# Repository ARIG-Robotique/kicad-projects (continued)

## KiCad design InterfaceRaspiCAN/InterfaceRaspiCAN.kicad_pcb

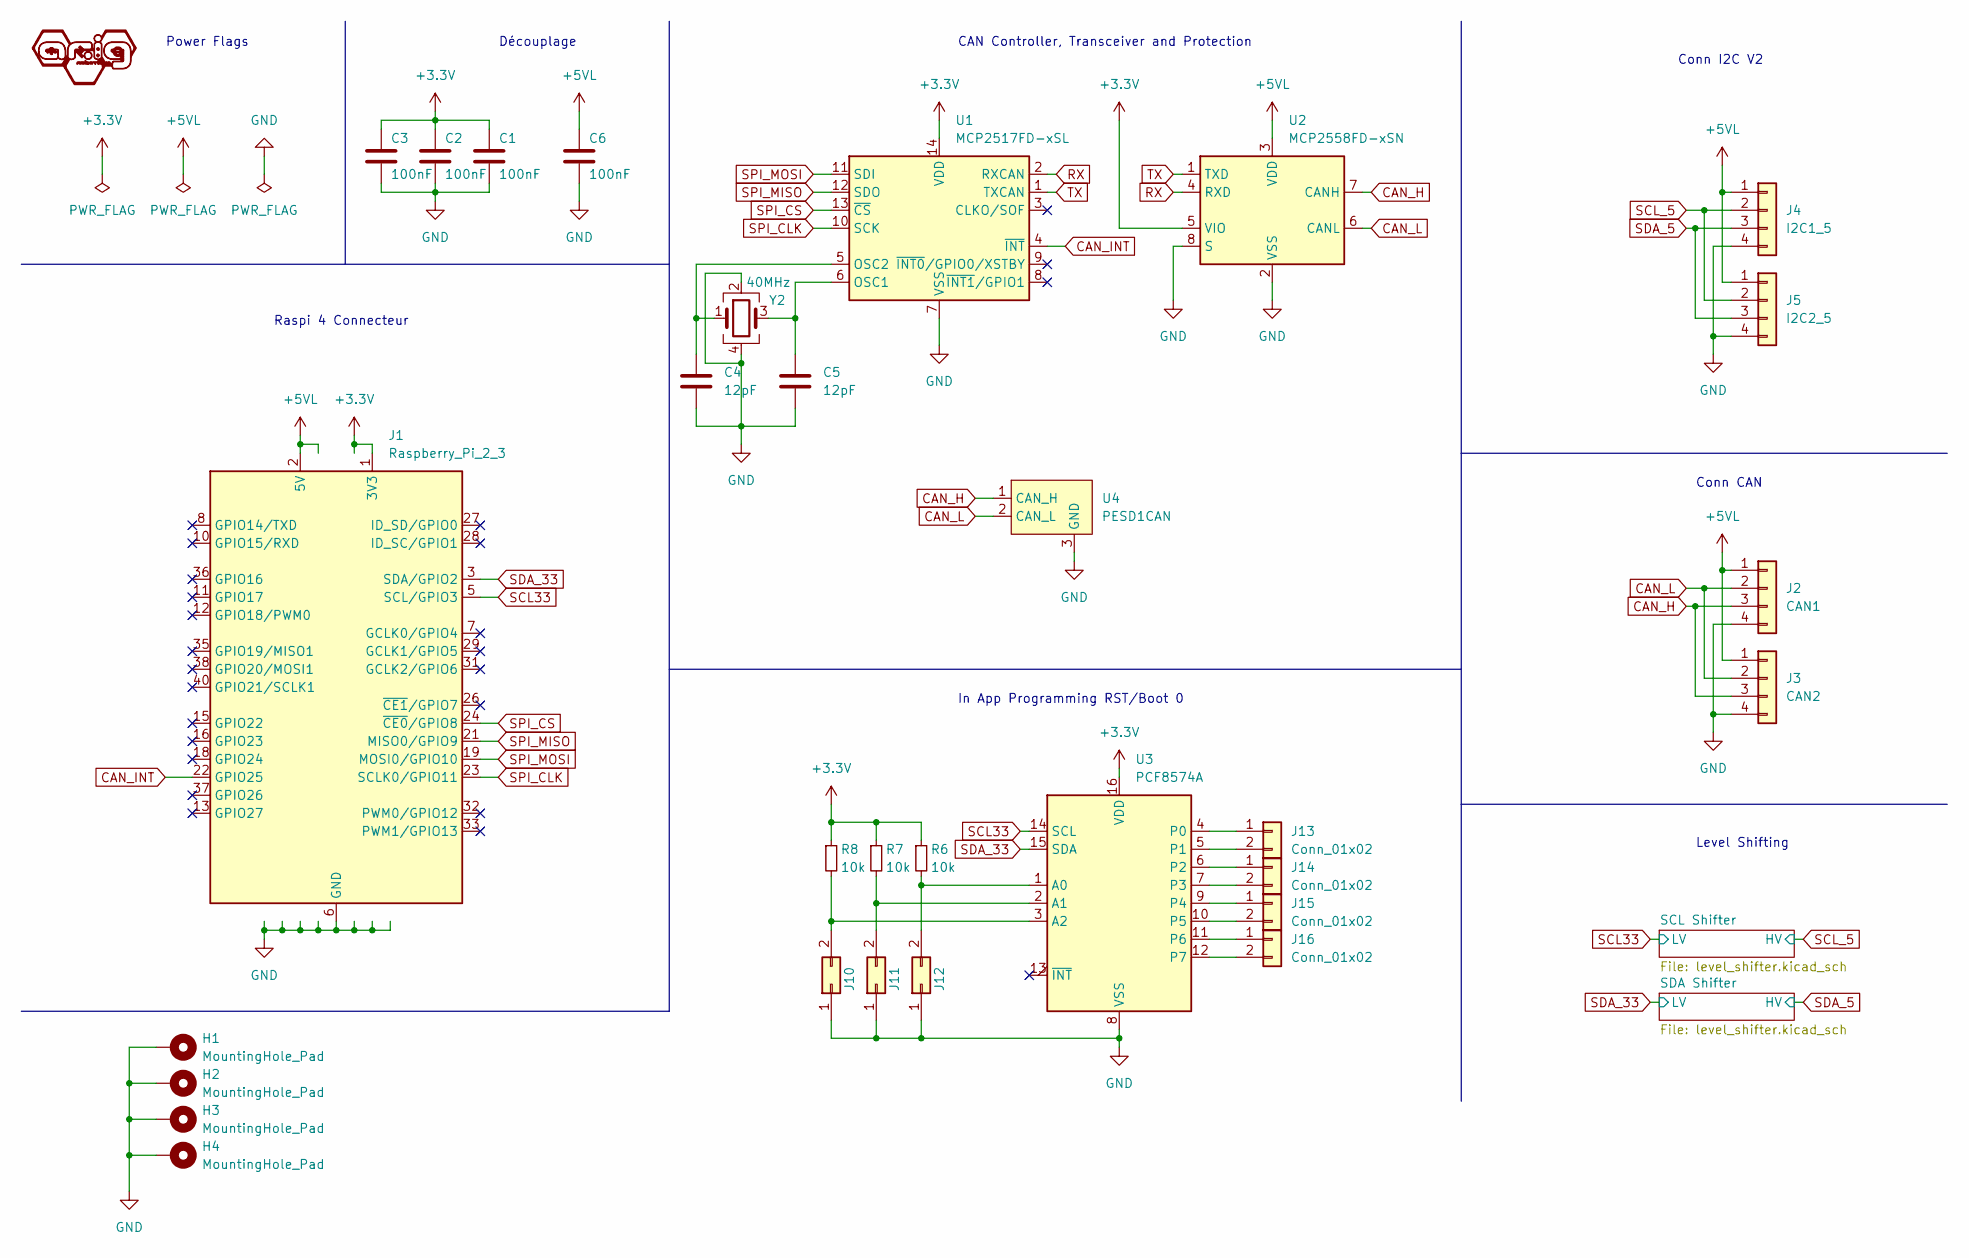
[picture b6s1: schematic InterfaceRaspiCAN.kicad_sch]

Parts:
C1, C2, C3, C6: 100nF; C_0402_1005Metric_Pad0.74x0.62mm_HandSolder; LCSC Part C1525
C4, C5: 12pF; C_0402_1005Metric_Pad0.74x0.62mm_HandSolder; LCSC Part C1547
H1, H2, H3, H4: MountingHole_Pad; MountingHole_2.7mm_M2.5_Pad_Via
J1: Raspberry_Pi_2_3; PinSocket_2x20_P2.54mm_Vertical
J2: CAN1; JST_PH_S4B-PH-K_1x04_P2.00mm_Horizontal
J3: CAN2; JST_PH_S4B-PH-K_1x04_P2.00mm_Horizontal
J4: I2C1_5; JST_PH_S4B-PH-K_1x04_P2.00mm_Horizontal
J5: I2C2_5; JST_PH_S4B-PH-K_1x04_P2.00mm_Horizontal
J10, J11, J12: Conn_02x01; SolderJumper-2_P1.3mm_Open_RoundedPad1.0x1.5mm
J13, J14, J15, J16: Conn_01x02; JST_PH_S2B-PH-K_1x02_P2.00mm_Horizontal
R6, R7, R8: 10k; R_0805_2012Metric_Pad1.20x1.40mm_HandSolder; LCSC Part C17414
U1: MCP2517FD-xSL; SOIC-14_3.9x8.7mm_P1.27mm; LCSC Part C133861
U2: MCP2558FD-xSN; SOIC-8_3.9x4.9mm_P1.27mm; LCSC Part C124015
U3: PCF8574A; SOIC-16W_7.5x10.3mm_P1.27mm; LCSC Part C7605
U4: PESD1CAN; SOT-23; LCSC Part C907838
Y2: 40MHz; Crystal_SMD_3225-4Pin_3.2x2.5mm_HandSoldering; LCSC Part C252255

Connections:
+3.3V: C1.1, C2.1, C3.1, J1.1 (3V3), J1.17 (3V3), R6.1, R7.1, R8.1, U1.14 (VDD), U2.5 (VIO), U3.16 (VDD); also elsewhere on the board
+5VL: C6.1, J1.2 (5V), J1.4 (5V), J2.1, J3.1, J4.1, J5.1, U2.3 (VDD); also elsewhere on the board
CAN_H: J2.3, J3.3, U2.7 (CANH), U4.1 (CAN_H)
CAN_INT: J1.22 (GPIO25), U1.4 (~INT)
CAN_L: J2.2, J3.2, U2.6 (CANL), U4.2 (CAN_L)
GND: C1.2, C2.2, C3.2, C4.2, C5.2, C6.2, H1.1, H2.1, H3.1, H4.1, J1.6 (GND), J1.9 (GND), J1.14 (GND), J1.20 (GND), J1.25 (GND), J1.30 (GND), J1.34 (GND), J1.39 (GND), J2.4, J3.4, J4.4, J5.4, J10.1, J11.1, J12.1, U1.7 (VSS), U2.2 (VSS), U2.8 (S), U3.8 (VSS), U4.3 (GND), Y2.2, Y2.4
unnamed: J10.2, R8.2, U3.3 (A2)
unnamed: J11.2, R7.2, U3.2 (A1)
unnamed: J12.2, R6.2, U3.1 (A0)
unnamed: J13.1, U3.4 (P0)
unnamed: J13.2, U3.5 (P1)
unnamed: J14.1, U3.6 (P2)
unnamed: J14.2, U3.7 (P3)
unnamed: J15.1, U3.9 (P4)
unnamed: J15.2, U3.10 (P5)
unnamed: J16.1, U3.11 (P6)
unnamed: J16.2, U3.12 (P7)
unnamed: C5.1, U1.6 (OSC1), Y2.3
unnamed: C4.1, U1.5 (OSC2), Y2.1
RX: U1.2 (RXCAN), U2.4 (RXD)
SCL33: J1.5 (SCL/GPIO3), U3.14 (SCL); also elsewhere on the board
SCL_5: J4.2, J5.2; also elsewhere on the board
SDA_5: J4.3, J5.3; also elsewhere on the board
SDA_33: J1.3 (SDA/GPIO2), U3.15 (SDA); also elsewhere on the board
SPI_CLK: J1.23 (SCLK0/GPIO11), U1.10 (SCK)
SPI_CS: J1.24 (~CE0/GPIO8), U1.13 (~CS)
SPI_MISO: J1.21 (MISO0/GPIO9), U1.12 (SDO)
SPI_MOSI: J1.19 (MOSI0/GPIO10), U1.11 (SDI)
TX: U1.1 (TXCAN), U2.1 (TXD)

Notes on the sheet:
In App Programming RST/Boot 0
Power Flags
Conn I2C V2
CAN Controller, Transceiver and Protection
Raspi 4 Connecteur
Level Shifting
Conn CAN
Découplage

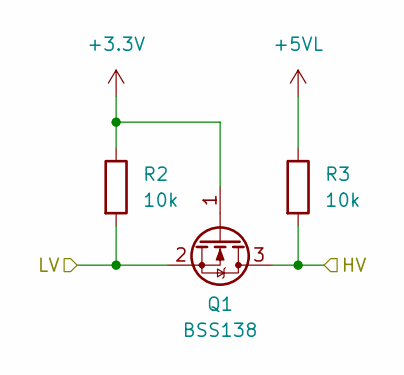
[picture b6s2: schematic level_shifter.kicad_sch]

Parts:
Q1: BSS138; SOT-23; LCSC Part C426569
R2, R3: 10k; R_0805_2012Metric_Pad1.20x1.40mm_HandSolder; LCSC Part C17414

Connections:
+3.3V: Q1.1 (G), R2.1; also elsewhere on the board
+5VL: R3.1; also elsewhere on the board
SCL33: Q1.2 (S), R2.2; also elsewhere on the board
SCL_5: Q1.3 (D), R3.2; also elsewhere on the board

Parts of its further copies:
Q2: BSS138; SOT-23; LCSC Part C426569
R4, R5: 10k; R_0805_2012Metric_Pad1.20x1.40mm_HandSolder; LCSC Part C17414

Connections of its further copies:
+3.3V: Q2.1 (G), R4.1; also elsewhere on the board
+5VL: R5.1; also elsewhere on the board
SDA_5: Q2.3 (D), R5.2; also elsewhere on the board
SDA_33: Q2.2 (S), R4.2; also elsewhere on the board

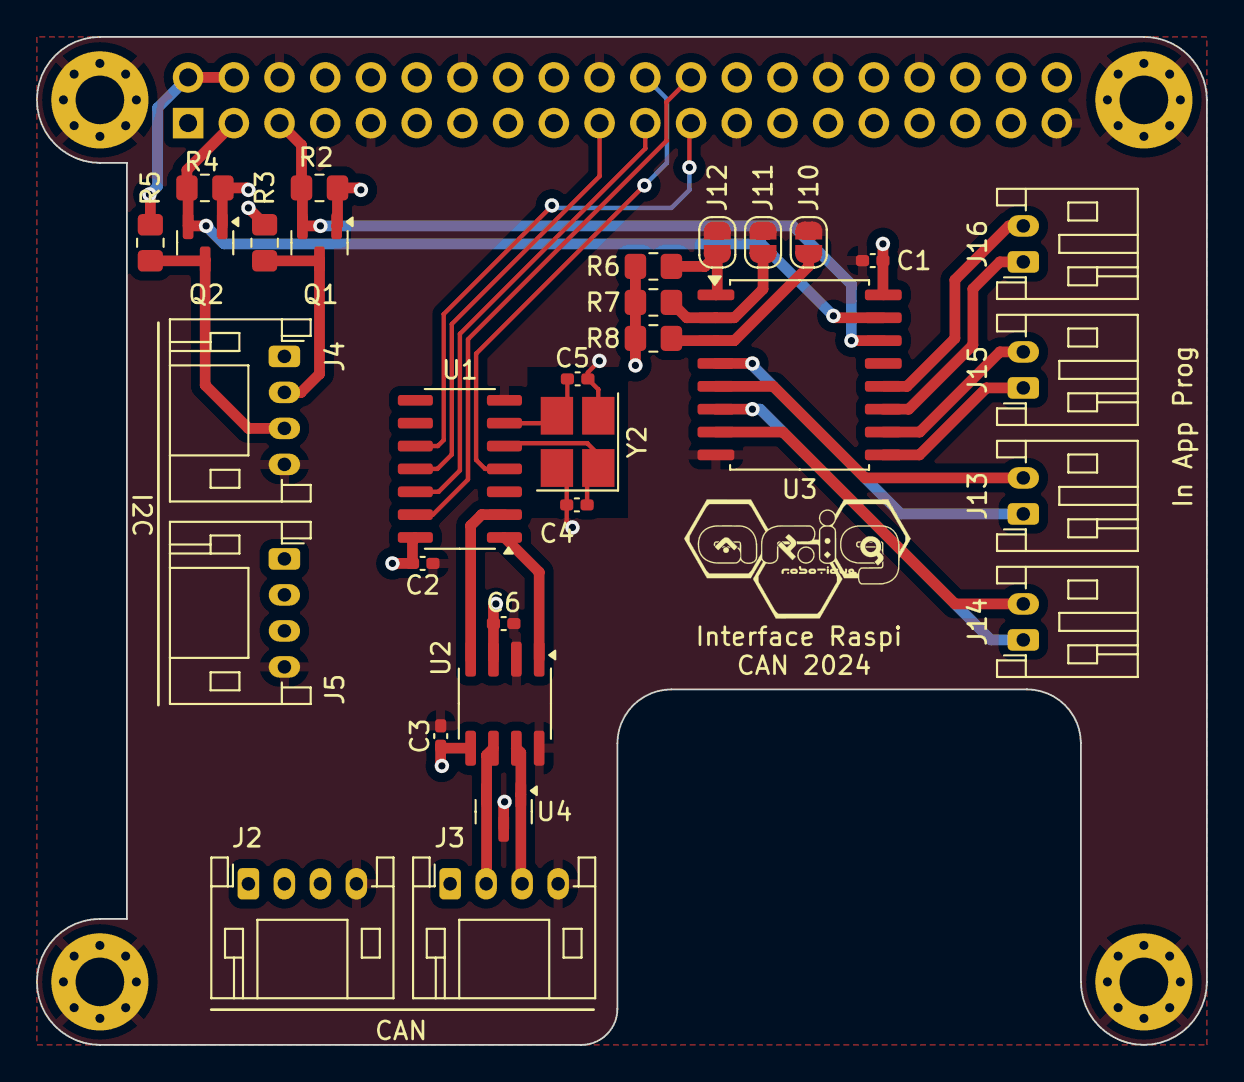
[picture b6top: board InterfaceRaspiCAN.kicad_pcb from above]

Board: 4 copper layers, 65.0 x 56.0 mm, 36 parts (1 on the bottom side), 29 nets.

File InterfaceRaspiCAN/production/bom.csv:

Designator,Footprint,Quantity,Value,LCSC Part #
"C1, C2, C3, C6",0402,4,100nF,C1525
"C4, C5",0402,2,12pF,C1547
"H1, H2, H3, H4",MountingHole_2.7mm_M2.5_Pad_Via,4,MountingHole_Pad,
J1,PinSocket_2x20_P2.54mm_Vertical,1,Raspberry_Pi_2_3,
"J10, J11, J12",SolderJumper-2_P1.3mm_Open_RoundedPad1.0x1.5mm,3,Conn_02x01,
"J13, J14, J15, J16",JST_PH_S2B-PH-K_1x02_P2.00mm_Horizontal,4,Conn_01x02,
J2,JST_PH_S4B-PH-K_1x04_P2.00mm_Horizontal,1,CAN1,
J3,JST_PH_S4B-PH-K_1x04_P2.00mm_Horizontal,1,CAN2,
J4,JST_PH_S4B-PH-K_1x04_P2.00mm_Horizontal,1,I2C1_5,
J5,JST_PH_S4B-PH-K_1x04_P2.00mm_Horizontal,1,I2C2_5,
"Q1, Q2",SOT-23,2,BSS138,C426569
"R2, R3, R4, R5, R6, R7, R8",0805,7,10k,C17414
U1,SOIC-14_3.9x8.7mm_P1.27mm,1,MCP2517FD-xSL,C133861
U2,SOIC-8_3.9x4.9mm_P1.27mm,1,MCP2558FD-xSN,C124015
U3,SOIC-16W_7.5x10.3mm_P1.27mm,1,PCF8574A,C7605
U4,SOT-23,1,PESD1CAN,C907838
Y2,Crystal_SMD_3225-4Pin_3.2x2.5mm_HandSoldering,1,40MHz, C252255

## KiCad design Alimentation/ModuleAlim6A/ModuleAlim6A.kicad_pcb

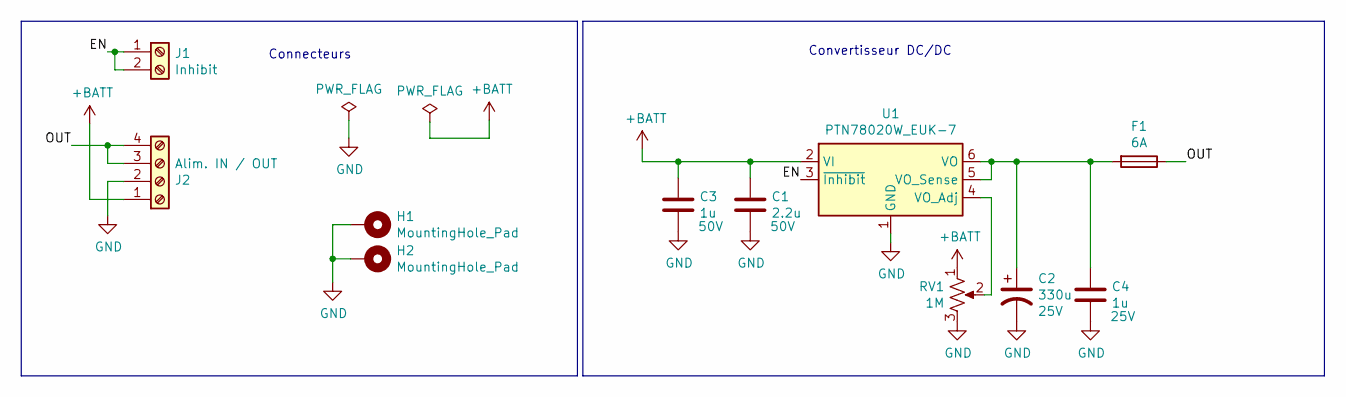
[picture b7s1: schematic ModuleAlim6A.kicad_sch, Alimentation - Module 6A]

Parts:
C1: 2.2u; C_1206_3216Metric_Pad1.33x1.80mm_HandSolder; LCSC Part C50254
C2: 330u; CP_Elec_8x10; LCSC Part C134842
C3: 1u; C_0805_2012Metric_Pad1.18x1.45mm_HandSolder; LCSC Part C28323
C4: 1u; C_0402_1005Metric_Pad0.74x0.62mm_HandSolder; LCSC Part C52923
F1: 6A; Fuseholder_Cylinder-5x20mm_Schurter_0031_8201_Horizontal_Op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; JLCPCB BOM 0
H1, H2: MountingHole_Pad; MountingHole_3.2mm_M3_Pad_Via; JLCPCB BOM 0
J1: Inhibit; TerminalBlock_Phoenix_MPT-0,5-2-2.54_1x02_P2.54mm_Horizontal; JLCPCB BOM 0
J2: Alim. IN / OUT; TerminalBlock_Phoenix_MKDS-1,5-4-5.08_1x04_P5.08mm_Horizont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; JLCPCB BOM 0
RV1: 1M; Potentiometer_Bourns_3266Y_Vertical; JLCPCB BOM 0
U1: PTN78020W_EUK-7; Texas_EUK_R-PDSS-T7_THT; JLCPCB BOM 0

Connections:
+BATT: C1.1, C3.1, J2.1, RV1.1, U1.2 (VI)
/EN: J1.1, J1.2, U1.3 (~Inhibit)
/OUT: F1.1, J2.3, J2.4
GND: C1.2, C2.2, C3.2, C4.2, H1.1, H2.1, J2.2, RV1.3, U1.1 (GND), U1.7 (GND)
unnamed: C2.1, C4.1, F1.2, U1.5 (VO_Sense), U1.6 (VO)
unnamed: RV1.2, U1.4 (VO_Adj)

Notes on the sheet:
Connecteurs
Convertisseur DC/DC

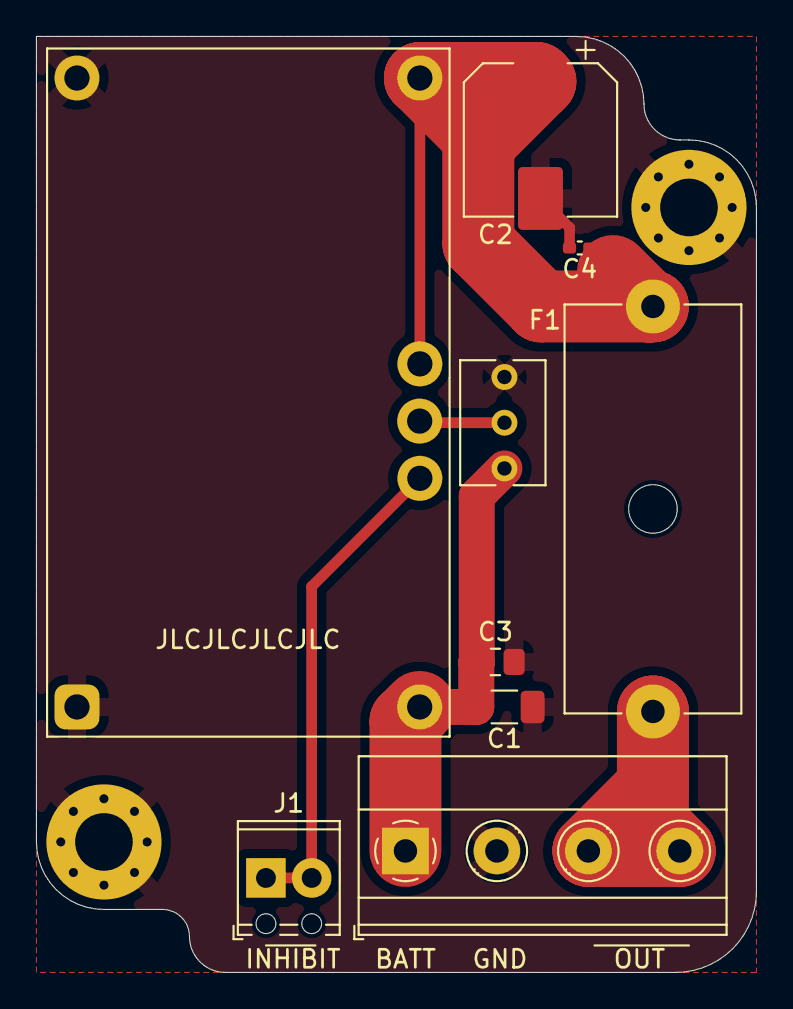
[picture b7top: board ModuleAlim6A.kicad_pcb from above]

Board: 2 copper layers, 40.0 x 52.0 mm, 11 parts (0 on the bottom side), 6 nets.

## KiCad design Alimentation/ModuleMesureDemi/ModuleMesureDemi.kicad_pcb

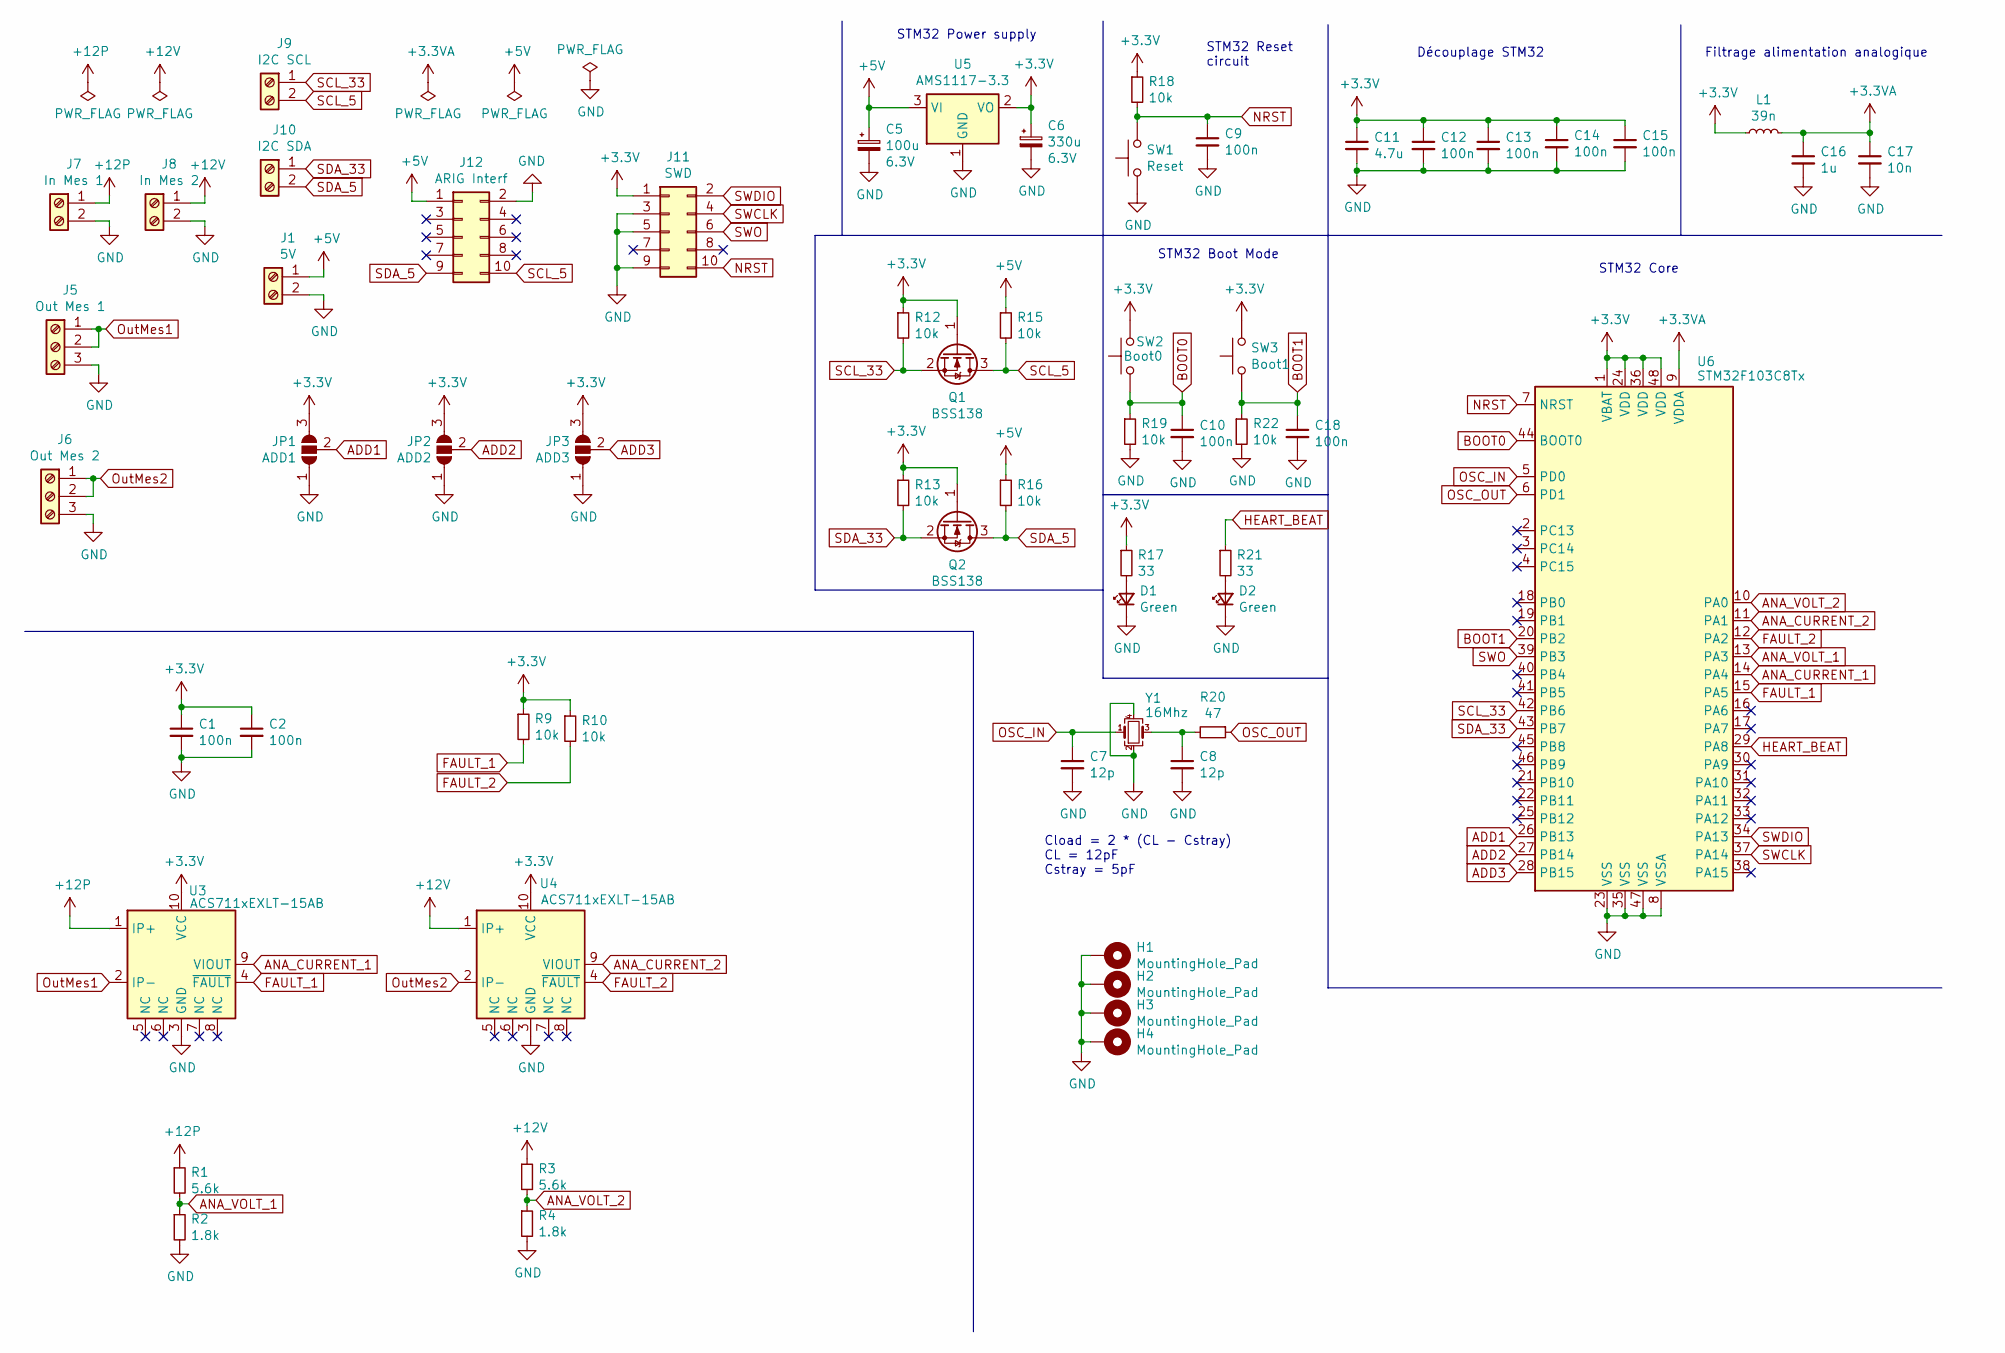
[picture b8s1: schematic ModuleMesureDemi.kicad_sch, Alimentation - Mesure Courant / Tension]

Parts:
C1, C2, C9, C10, C12, C13, C14, C15, C18: 100n; C_0402_1005Metric_Pad0.74x0.62mm_HandSolder; LCSC Part C1525
C5: 100u; CP_Elec_5x5.3; LCSC Part C249463
C6: 330u; CP_Elec_6.3x7.7; LCSC Part C249900
C7, C8: 12p; C_0402_1005Metric_Pad0.74x0.62mm_HandSolder; LCSC Part C1547
C11: 4.7u; C_0402_1005Metric_Pad0.74x0.62mm_HandSolder; LCSC Part C23733
C16: 1u; C_0402_1005Metric_Pad0.74x0.62mm_HandSolder; LCSC Part C52923
C17: 10n; C_0402_1005Metric_Pad0.74x0.62mm_HandSolder; LCSC Part C15195
D1, D2: Green; LED_0805_2012Metric_Pad1.15x1.40mm_HandSolder; LCSC Part C63855
H1, H2, H3, H4: MountingHole_Pad; MountingHole_3.2mm_M3_Pad_Via; JLCPCB BOM 0
J1: 5V; TerminalBlock_Phoenix_MPT-0,5-2-2.54_1x02_P2.54mm_Horizontal; JLCPCB BOM 0
J5: Out Mes 1; TerminalBlock_Phoenix_MKDS-1,5-3-5.08_1x03_P5.08mm_Horizont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; JLCPCB BOM 0
J6: Out Mes 2; TerminalBlock_Phoenix_MKDS-1,5-3-5.08_1x03_P5.08mm_Horizont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; JLCPCB BOM 0
J7: In Mes 1; TerminalBlock_Phoenix_MKDS-1,5-2-5.08_1x02_P5.08mm_Horizont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; JLCPCB BOM 0
J8: In Mes 2; TerminalBlock_Phoenix_MKDS-1,5-2-5.08_1x02_P5.08mm_Horizont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; JLCPCB BOM 0
J9: I2C SCL; TerminalBlock_Phoenix_MPT-0,5-2-2.54_1x02_P2.54mm_Horizontal; JLCPCB BOM 0
J10: I2C SDA; TerminalBlock_Phoenix_MPT-0,5-2-2.54_1x02_P2.54mm_Horizontal; JLCPCB BOM 0
J11: SWD; PinHeader_2x05_P1.27mm_Vertical; JLCPCB BOM 0
J12: ARIG Interf; IDC-Header_2x05_P2.54mm_Vertical; JLCPCB BOM 0
JP1: ADD1; SolderJumper-3_P1.3mm_Open_RoundedPad1.0x1.5mm; JLCPCB BOM 0
JP2: ADD2; SolderJumper-3_P1.3mm_Open_RoundedPad1.0x1.5mm; JLCPCB BOM 0
JP3: ADD3; SolderJumper-3_P1.3mm_Open_RoundedPad1.0x1.5mm; JLCPCB BOM 0
L1: 39n; L_0402_1005Metric_Pad0.77x0.64mm_HandSolder; LCSC Part C26443
Q1, Q2: BSS138; SOT-23; LCSC Part C112239
R1, R3: 5.6k; R_0805_2012Metric_Pad1.20x1.40mm_HandSolder; LCSC Part C26024
R2, R4: 1.8k; R_0805_2012Metric_Pad1.20x1.40mm_HandSolder; LCSC Part C17398
R9, R10, R12, R13, R15, R16, R18, R19, R22: 10k; R_0805_2012Metric_Pad1.20x1.40mm_HandSolder; LCSC Part C17414
R17, R21: 33; R_0805_2012Metric_Pad1.20x1.40mm_HandSolder; LCSC Part C17634
R20: 47; R_0402_1005Metric_Pad0.72x0.64mm_HandSolder; LCSC Part C25118
SW1: Reset; SW_SPST_B3U-1000P; LCSC Part C231329
SW2: Boot0; SW_SPST_B3U-1000P; LCSC Part C231329
SW3: Boot1; SW_SPST_B3U-1000P; LCSC Part C231329
U3, U4: ACS711xEXLT-15AB; Allegro_QFN-12-10-1EP_3x3mm_P0.5mm; LCSC Part C150824
U5: AMS1117-3.3; SOT-223-3_TabPin2; LCSC Part C6186
U6: STM32F103C8Tx; LQFP-48_7x7mm_P0.5mm; LCSC Part C8734
Y1: 16Mhz; Crystal_SMD_3225-4Pin_3.2x2.5mm_HandSoldering; LCSC Part C13738

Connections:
+3.3VA: C16.1, C17.1, L1.2, U6.9 (VDDA)
+3V3: C1.1, C2.1, C6.1, C11.1, C12.1, C13.1, C14.1, C15.1, J11.1, JP1.3 (B), JP2.3 (B), JP3.3 (B), L1.1, Q1.1 (G), Q2.1 (G), R9.1, R10.1, R12.1, R13.1, R17.1, R18.1, SW2.2, SW3.2, U3.10 (VCC), U4.10 (VCC), U5.2 (VO), U6.1 (VBAT), U6.24 (VDD), U6.36 (VDD), U6.48 (VDD)
+5V: C5.1, J1.1, J12.1, R15.1, R16.1, U5.3 (VI)
+12P: J7.1, R1.1, U3.1 (IP+)
+12V: J8.1, R3.1, U4.1 (IP+)
ADD1: JP1.2 (C), U6.26 (PB13)
ADD2: JP2.2 (C), U6.27 (PB14)
ADD3: JP3.2 (C), U6.28 (PB15)
ANA_CURRENT_1: U3.9 (VIOUT), U6.14 (PA4)
ANA_CURRENT_2: U4.9 (VIOUT), U6.11 (PA1)
ANA_VOLT_1: R1.2, R2.1, U6.13 (PA3)
ANA_VOLT_2: R3.2, R4.1, U6.10 (PA0)
BOOT0: C10.1, R19.1, SW2.1, U6.44 (BOOT0)
BOOT1: C18.1, R22.1, SW3.1, U6.20 (PB2)
FAULT_1: R9.2, U3.4 (~FAULT), U6.15 (PA5)
FAULT_2: R10.2, U4.4 (~FAULT), U6.12 (PA2)
GND: C1.2, C2.2, C5.2, C6.2, C7.2, C8.2, C9.2, C10.2, C11.2, C12.2, C13.2, C14.2, C15.2, C16.2, C17.2, C18.2, D1.1 (K), D2.1 (K), H1.1, H2.1, H3.1, H4.1, J1.2, J5.3, J6.3, J7.2, J8.2, J11.3, J11.5, J11.9, J12.2, JP1.1 (A), JP2.1 (A), JP3.1 (A), R2.2, R4.2, R19.2, R22.2, SW1.1, U3.3 (GND), U4.3 (GND), U5.1 (GND), U6.8 (VSSA), U6.23 (VSS), U6.35 (VSS), U6.47 (VSS), Y1.2, Y1.4
HEART_BEAT: R21.1, U6.29 (PA8)
NRST: C9.1, J11.10, R18.2, SW1.2, U6.7 (NRST)
unnamed: C8.1, R20.2, Y1.3
unnamed: D1.2 (A), R17.2
unnamed: D2.2 (A), R21.2
OSC_IN: C7.1, U6.5 (PD0), Y1.1
OSC_OUT: R20.1, U6.6 (PD1)
OutMes1: J5.1, J5.2, U3.2 (IP-)
OutMes2: J6.1, J6.2, U4.2 (IP-)
SCL_5: J9.2, J12.10, Q1.3 (D), R15.2
SCL_33: J9.1, Q1.2 (S), R12.2, U6.42 (PB6)
SDA_5: J10.2, J12.9, Q2.3 (D), R16.2
SDA_33: J10.1, Q2.2 (S), R13.2, U6.43 (PB7)
SWCLK: J11.4, U6.37 (PA14)
SWDIO: J11.2, U6.34 (PA13)
SWO: J11.6, U6.39 (PB3)

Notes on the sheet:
Découplage STM32
STM32 Reset circuit
STM32 Boot Mode
STM32 Core
STM32 Power supply
Cload = 2 * (CL - Cstray) CL = 12pF Cstray = 5pF
Filtrage alimentation analogique

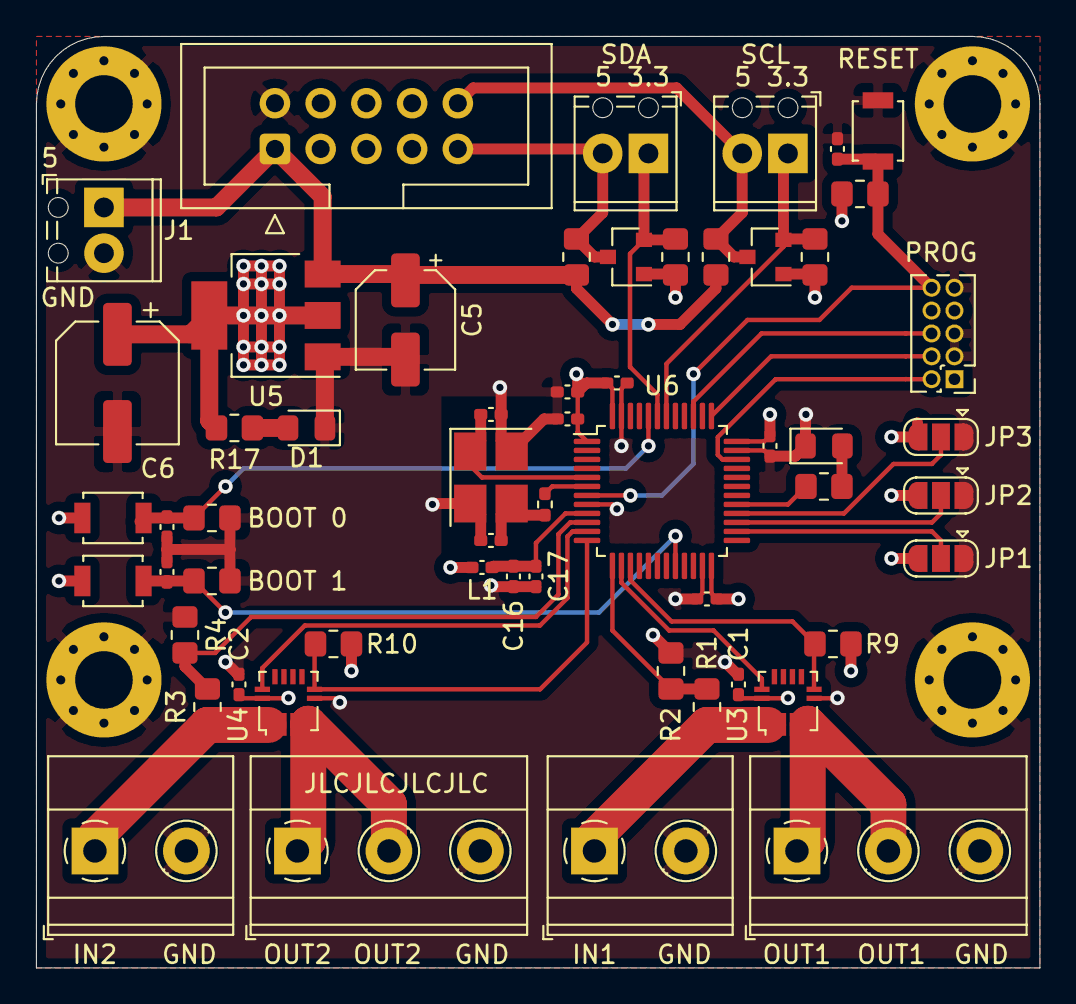
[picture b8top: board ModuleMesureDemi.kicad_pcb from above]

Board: 4 copper layers, 55.8 x 51.8 mm, 61 parts (0 on the bottom side), 33 nets.

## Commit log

2020-11-18 Carte capteur numérique SMD
2020-11-25 Master alimentation SMD
2020-11-25 Capteurs num production
2020-11-25 Library & footprints
2020-11-26 Dimensionnement et récupération des part LCSC
2020-11-30 Finalisation routage carte alim maitre
2020-11-30 Ajout logo ARIG pour la sérigraphie
2020-11-30 Module alimentation 6A
2020-12-01 Alim STm32 + module 3A
2020-12-07 Module alim ISO, clean master alim
2020-12-10 Modules Alim 3A et 6A uniforme sans mesure courant/tension
2020-12-13 Finalisation modules 3A et 6A, routage master alim
2020-12-15 Finalisation routage master alim
2020-12-15 Ignore fichier step
2020-12-17 Rework suite point robot
2020-12-17 Init module alimentation mesure
2021-01-17 Finalisation alimentations
2021-01-17 Carte de mesure de courant et de tension
2021-02-15 Finalisation pour commande pack Alimentation 14/02/2021
2021-02-26 Multiplexeur de capteur couleur (TCS34725)
    # Liste des mots clés de titre de commit (version courte -> résultat long)
    # r <num> -> Récupération du Redmine (Redmine #<num> : <titre_du_redmine>)
    # t <titre> -> Technique : <titre>
    # f <titre> -> Fix : <titre>
    # ty <titre> -> Typo : <titre>
    # d <titre> -> Doc : <titre>
2021-03-11 Potar THT module 3A
    # Liste des mots clés de titre de commit (version courte -> résultat long)
    # r <num> -> Récupération du Redmine (Redmine #<num> : <titre_du_redmine>)
    # t <titre> -> Technique : <titre>
    # f <titre> -> Fix : <titre>
    # ty <titre> -> Typo : <titre>
    # d <titre> -> Doc : <titre>
2021-03-20 Contrôleur de pompes à vide autonome
    # Liste des mots clés de titre de commit (version courte -> résultat long)
    # r <num> -> Récupération du Redmine (Redmine #<num> : <titre_du_redmine>)
    # t <titre> -> Technique : <titre>
    # f <titre> -> Fix : <titre>
    # ty <titre> -> Typo : <titre>
    # d <titre> -> Doc : <titre>
2021-03-22 Interfaces Raspberry PI
    # Liste des mots clés de titre de commit (version courte -> résultat long)
    # r <num> -> Récupération du Redmine (Redmine #<num> : <titre_du_redmine>)
    # t <titre> -> Technique : <titre>
    # f <titre> -> Fix : <titre>
    # ty <titre> -> Typo : <titre>
    # d <titre> -> Doc : <titre>
2021-04-07 Ajout des rendus 3D
2021-04-08 Réduction de taille rail alimentation (fusion borniers)
2021-04-08 Ajout bornier alim 5V sur controleur pompes
2021-04-08 Finalisation interf Raspi
2021-04-08 Ajout bornier alim 5V sur multiplexeur couleur
2021-04-18 Finalisation multiplexeur couleur
2021-04-18 Finalisation interface Raspi
2021-04-18 Re génération des modules alim pour le README
2021-04-18 Ajout empreinte pour switch tactile SMD TS 1088
2021-04-18 Ajout 4 inputs TOR sur le contrôleur pompes
2021-04-18 Finalisation rail alimentation
2021-04-22 Fix Master Alim : affichage statut AU
2021-04-22 Fix module alim 3A : sérigraphie
2021-04-22 Fix images rikiki
2021-05-02 Erreur entre la sérigraphie et l'assignation des PIN
2021-12-12 Ajout Seeeduino XIAO
2021-12-12 Init projet pour la détection des carrés de fouilles
2021-12-12 Cache controlleurs pompes
2022-03-08 Ajout du PCB de detection des carrés de fouilles
2022-03-13 Kicad 6 symbol library
2022-03-13 Arduino Nano 3D model
2022-03-13 Detecteur Carre fouille (pour 2022 en tous cas)
2022-03-24 Répertoire de sortie des fichiers de production
2023-12-11 Add HAT Raspi with CAN, In App Prog and I2C
2023-12-11 Upgrade symbol library to Kicad 7
2023-12-11 Add symbol PESD1CAN (can bus electrostatic protection)
2023-12-12 Fix footprint for PCF8575
2023-12-12 Add PCB for RaspiCAN
2023-12-14 Add ignore for KiCad 7 format
2023-12-14 Upgrade to KiCad 7 some PCB
    - MasterAlimSTM32
    - Capteurs numerique
    - Controleurs pompes
    - Detecteur carre fouille
    - Interface Raspi (without CAN)
2023-12-14 Changes from discussion on meetings
    - Remove 2x I2C connectors
    - Remove 4x InApp programming connectors
    - Change PCF8575 to PCF8574
    - Change a half connectors to horizontal version
2023-12-20 Init project for Asserv Controller
2023-12-21 Upgrade vacuum controller
2023-12-21 Modification for InterfaceRaspiCAN
2023-12-21 Move asserv controller to the right place
2024-01-01 Upgrade base schematics
2024-01-01 Add template for STM32 with CAN
2024-01-03 Add coders & motors interface
2024-01-03 Finalize placement for AsservController
2024-01-03 Change inApp prog, CAN & I2C connectors
2024-01-08 Init routing
2024-01-16 Upgrade alim to Kicad 7
2024-01-16 Add routing on controller asserv
2024-01-16 Add master alim CAN
2024-01-16 Update MasterAlim to Kicad 7
2024-01-16 Update ModuleMesure to Kicad 7
2024-01-18 Add some routes to ControlleursAsserv
2024-02-06 Upgrade AlimMesureDemi to Kicad 7
2024-02-06 Upgrade module Alim6A to Kicad7
2024-02-06 Restructure schematics of AlimCAN
2024-02-07 Add size value in layer comments
2024-02-07 Init placement for MasterAlimCAN
2024-02-07 Last save for today
2024-02-07 Fix 3D model for Texas DC/DC converters
2024-02-07 New disposition for alim CAN
2024-02-24 Fix base PCB STM32 CAN
2024-02-24 Finish Controller Asserv
2024-02-24 In app programming on 3.3V
2024-02-24 New placement for Alim
2024-02-27 Fix CAN connections to improve routing on Base Board
2024-02-27 Fix CAN connections to improve routing on ControllerAsserv
2024-02-27 Fix CAN connections to improve routing on InterfaceRaspi
2024-02-27 Finish component placement on MasterAlimCAN
2024-03-06 Upgrade to KicCad 8
2024-03-06 Upgrade to KiCad 8 and finish routing
    - MasterAlimCAN
    - InterfaceRaspiCAN
2024-03-08 Board to adapt PAMI motor with others boards
2024-03-08 Step generation of motor adaptor
2024-03-11 Generate all production files
2024-04-11 Convert old schematics
2025-04-15 Upgrade to KiCad 9 a small piece of projects
2025-04-15 Generate a dummy Codeurs V2 to have 3D model to use inside SolidWorks
